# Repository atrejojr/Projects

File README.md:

# Projects

Hi!

This holds some of the projects I made throughout my time in college. These projects range from logic design using Verilog to circuit design utilizing KiCad.

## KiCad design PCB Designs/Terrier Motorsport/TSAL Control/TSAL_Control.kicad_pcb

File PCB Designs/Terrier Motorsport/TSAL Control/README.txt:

Project Description:

The TSAL Control system, like its name says, controls the Tractive System Active Light (TSAL). Based on the SAE Formula Hybrid + Electric (2025 v1) rule book, there are a few things to consider when designing this control board. It is important to note that this system is not a part of the shutdown loop but serves to warn those around the vehicle that there is high voltage present. This board is only active when high voltage is present outside the AIR coils. In our case, the TS Stepdown will only activate when the HV system is above 100V, so we do not need to integrate voltage comparators or any type of galvanic isolation. The TSAL will flash red at a frequency of 2-5Hz.

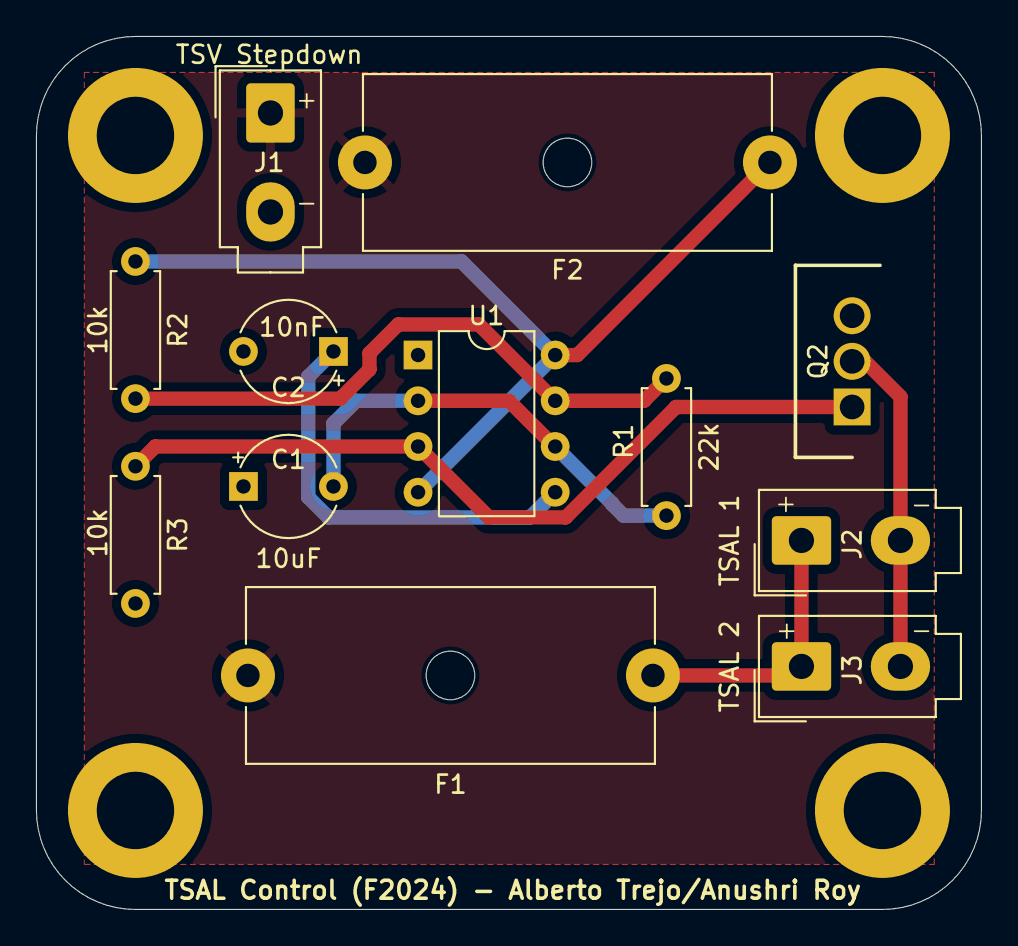
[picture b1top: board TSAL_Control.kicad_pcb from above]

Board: 2 copper layers, 52.5 x 48.5 mm, 12 parts (0 on the bottom side), 9 nets.

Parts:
C1: 10uF; CP_Radial_Tantal_D5.5mm_P5.00mm
C2: 10nF; CP_Radial_Tantal_D5.5mm_P5.00mm
F1: 500mA Fuse; Fuseholder_Cylinder-5x20mm_Schurter_0031_8201_Horizontal_Op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
F2: ??? Fuse; Fuseholder_Cylinder-5x20mm_Schurter_0031_8201_Horizontal_Op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
J1: TSV Stepdown; Molex_Mini-Fit_Jr_5566-02A_2x01_P4.20mm_Vertical
J2: TSAL 1; U-Lite
J3: TSAL 2; U-Lite
Q2: NMOS; FQ30N06L_Motorsport
R1: 22k; R_Axial_DIN0207_L6.3mm_D2.5mm_P7.62mm_Horizontal_Motorsport
R2, R3: 10k; R_Axial_DIN0207_L6.3mm_D2.5mm_P7.62mm_Horizontal_Motorsport
U1: NE555P; DIP-8_W7.62mm

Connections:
/12V: F1.1, F2.1, J1.1
unnamed: F1.2, J2.2 (A), J3.2 (A)
unnamed: J2.1 (K), J3.1 (K), Q2.2 (D)
unnamed: Q2.1 (G), R3.1, U1.3 (Q)
unnamed: C2.1, U1.5 (CV)
unnamed: R1.2, R2.1, U1.7 (DIS)
unnamed: F2.2, R2.2, U1.4 (R), U1.8 (VCC)
unnamed: C1.2, R1.1, U1.2 (TR), U1.6 (THR)
TSVSD-: C1.1, C2.2, J1.2, Q2.3 (S), R3.2, U1.1 (GND)

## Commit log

2024-11-06 Create Logic Design
2024-11-06 Create EC 311 Lab 1
2024-11-06 Create Codes
2024-11-06 Create Code
2024-12-02 Rename Logic presentation.pptx to Slideshow
2025-04-01 Create file1
2025-04-01 Backups
2025-04-01 Fixed back-up folder
2025-04-05 Created style.css
2025-08-16 Rename README.md to readme.md
2025-08-16 Rename Personal Coding Projects/C_C++/Code to Personal Coding Projects/C_C++/Clock/main.c
2025-08-16 testing out compiler
2025-08-17 1:03:55 time stamp
2025-08-17 Renamed and organized a few folders
2025-08-17 laptop broke, saving progress
